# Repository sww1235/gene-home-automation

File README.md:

# gene-home-automation
Home Automation stuff for my grandfathers house

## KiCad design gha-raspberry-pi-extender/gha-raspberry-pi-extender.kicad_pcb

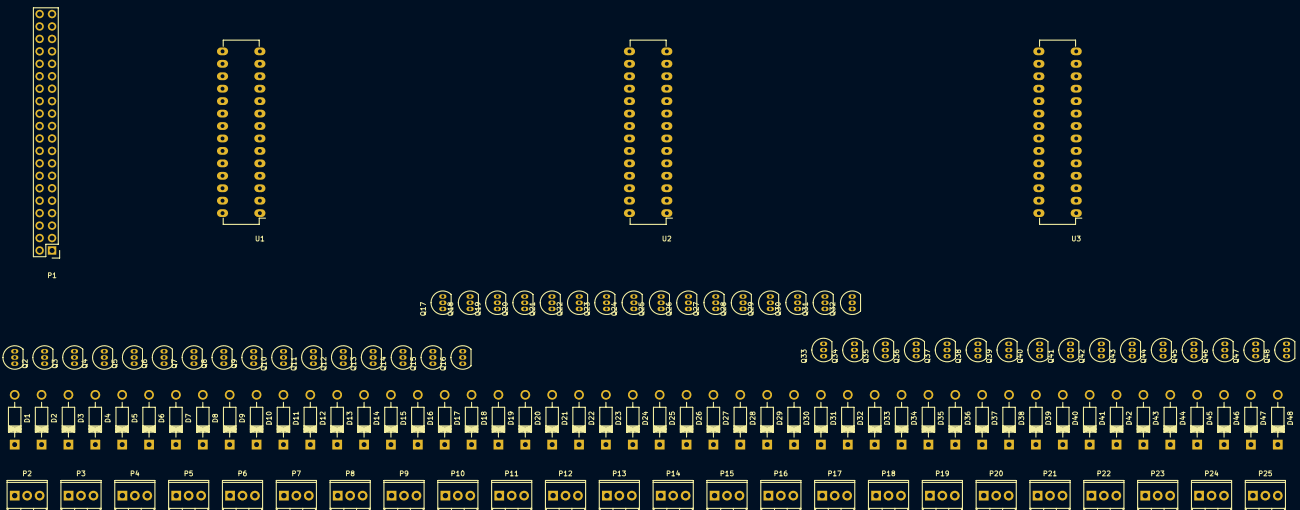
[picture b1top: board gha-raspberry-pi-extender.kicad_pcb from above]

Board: 2 copper layers, 124 parts (0 on the bottom side), 100 nets, no tracks yet.

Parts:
D1, D2, D3, D4, D5, D6, D7, D8, D9, D10, D11, D12, D13, D14, D15, D16, D17, D18, D19, D20, D21, D22, D23, D24, D25, D26, D27, D28, D29, D30, D31, D32, D33, D34, D35, D36, D37, D38, D39, D40, D41, D42, D43, D44, D45, D46, D47, D48: 1N4001; Diode_DO-41_SOD81_Horizontal_RM10
P1: RaspberryPi-GPIO-header-logical; Pin_Header_Straight_2x20
P2, P10, P18: Relay 1; TerminalBlock_Pheonix_MPT-2.54mm_3pol
P3, P11, P19: Relay 2; TerminalBlock_Pheonix_MPT-2.54mm_3pol
P4, P12, P20: Relay 3; TerminalBlock_Pheonix_MPT-2.54mm_3pol
P5, P13, P21: Relay 4; TerminalBlock_Pheonix_MPT-2.54mm_3pol
P6, P14, P22: Relay 5; TerminalBlock_Pheonix_MPT-2.54mm_3pol
P7, P15, P23: Relay 6; TerminalBlock_Pheonix_MPT-2.54mm_3pol
P8, P16, P24: Relay 7; TerminalBlock_Pheonix_MPT-2.54mm_3pol
P9, P17, P25: Relay 8; TerminalBlock_Pheonix_MPT-2.54mm_3pol
Q1, Q2, Q3, Q4, Q5, Q6, Q7, Q8, Q9, Q10, Q11, Q12, Q13, Q14, Q15, Q16, Q17, Q18, Q19, Q20, Q21, Q22, Q23, Q24, Q25, Q26, Q27, Q28, Q29, Q30, Q31, Q32, Q33, Q34, Q35, Q36, Q37, Q38, Q39, Q40, Q41, Q42, Q43, Q44, Q45, Q46, Q47, Q48: BS170; TO-92_Inline_Narrow_Oval
U1, U2, U3: MCP23017; DIP-28_W7.62mm_LongPads

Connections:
+5V: P1.2, P1.4, U1.10, U2.10, U2.15, U3.10, U3.16
/Relay Bank 1/Relay-1-Closed: Q2.2, U1.22
/Relay Bank 1/Relay-1-Open: Q1.2, U1.21
/Relay Bank 1/Relay-2-Closed: Q4.2, U1.24
/Relay Bank 1/Relay-2-Open: Q3.2, U1.23
/Relay Bank 1/Relay-3-Closed: Q6.2, U1.26
/Relay Bank 1/Relay-3-Open: Q5.2, U1.25
/Relay Bank 1/Relay-4-Closed: Q8.2, U1.28
/Relay Bank 1/Relay-4-Open: Q7.2, U1.27
/Relay Bank 1/Relay-5-Closed: Q10.2, U1.2
/Relay Bank 1/Relay-5-Open: Q9.2, U1.1
/Relay Bank 1/Relay-6-Closed: Q12.2, U1.4
/Relay Bank 1/Relay-6-Open: Q11.2, U1.3
/Relay Bank 1/Relay-7-Closed: Q14.2, U1.6
/Relay Bank 1/Relay-7-Open: Q13.2, U1.5
/Relay Bank 1/Relay-8-Closed: Q16.2, U1.8
/Relay Bank 1/Relay-8-Open: Q15.2, U1.7
/Relay Bank 1/SCL: P1.5, U1.13, U2.13, U3.13
/Relay Bank 1/SDA: P1.3, U1.12, U2.12, U3.12
/Relay Bank 2/Relay-1-Closed: Q18.2, U2.22
/Relay Bank 2/Relay-1-Open: Q17.2, U2.21
/Relay Bank 2/Relay-2-Closed: Q20.2, U2.24
/Relay Bank 2/Relay-2-Open: Q19.2, U2.23
/Relay Bank 2/Relay-3-Closed: Q22.2, U2.26
/Relay Bank 2/Relay-3-Open: Q21.2, U2.25
/Relay Bank 2/Relay-4-Closed: Q24.2, U2.28
/Relay Bank 2/Relay-4-Open: Q23.2, U2.27
/Relay Bank 2/Relay-5-Closed: Q26.2, U2.2
/Relay Bank 2/Relay-5-Open: Q25.2, U2.1
/Relay Bank 2/Relay-6-Closed: Q28.2, U2.4
/Relay Bank 2/Relay-6-Open: Q27.2, U2.3
/Relay Bank 2/Relay-7-Closed: Q30.2, U2.6
/Relay Bank 2/Relay-7-Open: Q29.2, U2.5
/Relay Bank 2/Relay-8-Closed: Q32.2, U2.8
/Relay Bank 2/Relay-8-Open: Q31.2, U2.7
/Relay Bank 3/Relay-1-Closed: Q34.2, U3.22
/Relay Bank 3/Relay-1-Open: Q33.2, U3.21
/Relay Bank 3/Relay-2-Closed: Q36.2, U3.24
/Relay Bank 3/Relay-2-Open: Q35.2, U3.23
/Relay Bank 3/Relay-3-Closed: Q38.2, U3.26
/Relay Bank 3/Relay-3-Open: Q37.2, U3.25
/Relay Bank 3/Relay-4-Closed: Q40.2, U3.28
/Relay Bank 3/Relay-4-Open: Q39.2, U3.27
/Relay Bank 3/Relay-5-Closed: Q42.2, U3.2
/Relay Bank 3/Relay-5-Open: Q41.2, U3.1
/Relay Bank 3/Relay-6-Closed: Q44.2, U3.4
/Relay Bank 3/Relay-6-Open: Q43.2, U3.3
/Relay Bank 3/Relay-7-Closed: Q46.2, U3.6
/Relay Bank 3/Relay-7-Open: Q45.2, U3.5
/Relay Bank 3/Relay-8-Closed: Q48.2, U3.8
/Relay Bank 3/Relay-8-Open: Q47.2, U3.7
GNDREF: P1.6, P1.9, P1.14, P1.20, P1.25, P1.30, P1.34, P1.39, P2.2, P3.2, P4.2, P5.2, P6.2, P7.2, P8.2, P9.2, P10.2, P11.2, P12.2, P13.2, P14.2, P15.2, P16.2, P17.2, P18.2, P19.2, P20.2, P21.2, P22.2, P23.2, P24.2, P25.2, Q1.3, Q2.3, Q3.3, Q4.3, Q5.3, Q6.3, Q7.3, Q8.3, Q9.3, Q10.3, Q11.3, Q12.3, Q13.3, Q14.3, Q15.3, Q16.3, Q17.3, Q18.3, Q19.3, Q20.3, Q21.3, Q22.3, Q23.3, Q24.3, Q25.3, Q26.3, Q27.3, Q28.3, Q29.3, Q30.3, Q31.3, Q32.3, Q33.3, Q34.3, Q35.3, Q36.3, Q37.3, Q38.3, Q39.3, Q40.3, Q41.3, Q42.3, Q43.3, Q44.3, Q45.3, Q46.3, Q47.3, Q48.3, U1.9, U1.15, U1.16, U1.17, U2.9, U2.16, U2.17, U3.9, U3.15, U3.17
unnamed: D1.1, D1.2, P2.1, Q1.1
unnamed: D2.1, D2.2, P2.3, Q2.1
unnamed: D3.1, D3.2, P3.1, Q3.1
unnamed: D4.1, D4.2, P3.3, Q4.1
unnamed: D5.1, D5.2, P4.1, Q5.1
unnamed: D6.1, D6.2, P4.3, Q6.1
unnamed: D7.1, D7.2, P5.1, Q7.1
unnamed: D8.1, D8.2, P5.3, Q8.1
unnamed: D9.1, D9.2, P6.1, Q9.1
unnamed: D10.1, D10.2, P6.3, Q10.1
unnamed: D11.1, D11.2, P7.1, Q11.1
unnamed: D12.1, D12.2, P7.3, Q12.1
unnamed: D13.1, D13.2, P8.1, Q13.1
unnamed: D14.1, D14.2, P8.3, Q14.1
unnamed: D15.1, D15.2, P9.1, Q15.1
unnamed: D16.1, D16.2, P9.3, Q16.1
unnamed: D17.1, D17.2, P10.1, Q17.1
unnamed: D18.1, D18.2, P10.3, Q18.1
unnamed: D19.1, D19.2, P11.1, Q19.1
unnamed: D20.1, D20.2, P11.3, Q20.1
unnamed: D21.1, D21.2, P12.1, Q21.1
unnamed: D22.1, D22.2, P12.3, Q22.1
unnamed: D23.1, D23.2, P13.1, Q23.1
unnamed: D24.1, D24.2, P13.3, Q24.1
unnamed: D25.1, D25.2, P14.1, Q25.1
unnamed: D26.1, D26.2, P14.3, Q26.1
unnamed: D27.1, D27.2, P15.1, Q27.1
unnamed: D28.1, D28.2, P15.3, Q28.1
unnamed: D29.1, D29.2, P16.1, Q29.1
unnamed: D30.1, D30.2, P16.3, Q30.1
unnamed: D31.1, D31.2, P17.1, Q31.1
unnamed: D32.1, D32.2, P17.3, Q32.1
unnamed: D33.1, D33.2, P18.1, Q33.1
unnamed: D34.1, D34.2, P18.3, Q34.1
unnamed: D35.1, D35.2, P19.1, Q35.1
unnamed: D36.1, D36.2, P19.3, Q36.1
unnamed: D37.1, D37.2, P20.1, Q37.1
unnamed: D38.1, D38.2, P20.3, Q38.1
unnamed: D39.1, D39.2, P21.1, Q39.1
unnamed: D40.1, D40.2, P21.3, Q40.1
unnamed: D41.1, D41.2, P22.1, Q41.1
unnamed: D42.1, D42.2, P22.3, Q42.1
unnamed: D43.1, D43.2, P23.1, Q43.1
unnamed: D44.1, D44.2, P23.3, Q44.1
unnamed: D45.1, D45.2, P24.1, Q45.1
unnamed: D46.1, D46.2, P24.3, Q46.1
unnamed: D47.1, D47.2, P25.1, Q47.1
unnamed: D48.1, D48.2, P25.3, Q48.1

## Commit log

2016-12-19 initial commit, added gitignore
2016-12-19 adding project files
2016-12-20 finished schematic and started pcb layout
2016-12-20 fixed some schematic issues
2016-12-20 added mouser bom
2016-12-20 updated gitignore
2016-12-21 added relays to control AC voltages
2016-12-21 added RPi notes
2016-12-23 fucked up where I git inited
2016-12-23 some more fixings
2016-12-23 added permisson file
2016-12-23 renaming file
2016-12-23 finished the pi config part 1 for now
2016-12-23 initial lambda function from desert-home
2016-12-23 committing everything before taking a break
2016-12-26 added skill-intent example file
2016-12-26 started on the alexa skill documetation
2016-12-26 finished skill-intents json
2016-12-26 changed capitilization of intent name
2016-12-26 finished alexa skills section
2016-12-27 begining pi code
2016-12-27 updated lambda stuff
2016-12-27 added mytime.py
2016-12-28 added some documentation
2016-12-28 added docstrings and fixed whitespace errors
2016-12-28 removed lint
2016-12-28 started work on physical setup
2016-12-29 potential final commit before giving first draft to gene
2016-12-29 final commit on documentation before pi code complete
2016-12-29 renaming references file
2016-12-29 update references
2016-12-29 removed a few links
2016-12-29 updating rpi-process
2016-12-29 added awsiot to first amazon config
2016-12-29 added gitignore
2016-12-29 updated adding user instructions
2016-12-29 updated permissions stuff for user
2016-12-29 fixed roles and permissions
2016-12-29 fixed bracket error
2016-12-29 modififed gitignore
2016-12-29 update gitignore
2016-12-29 updated python code
